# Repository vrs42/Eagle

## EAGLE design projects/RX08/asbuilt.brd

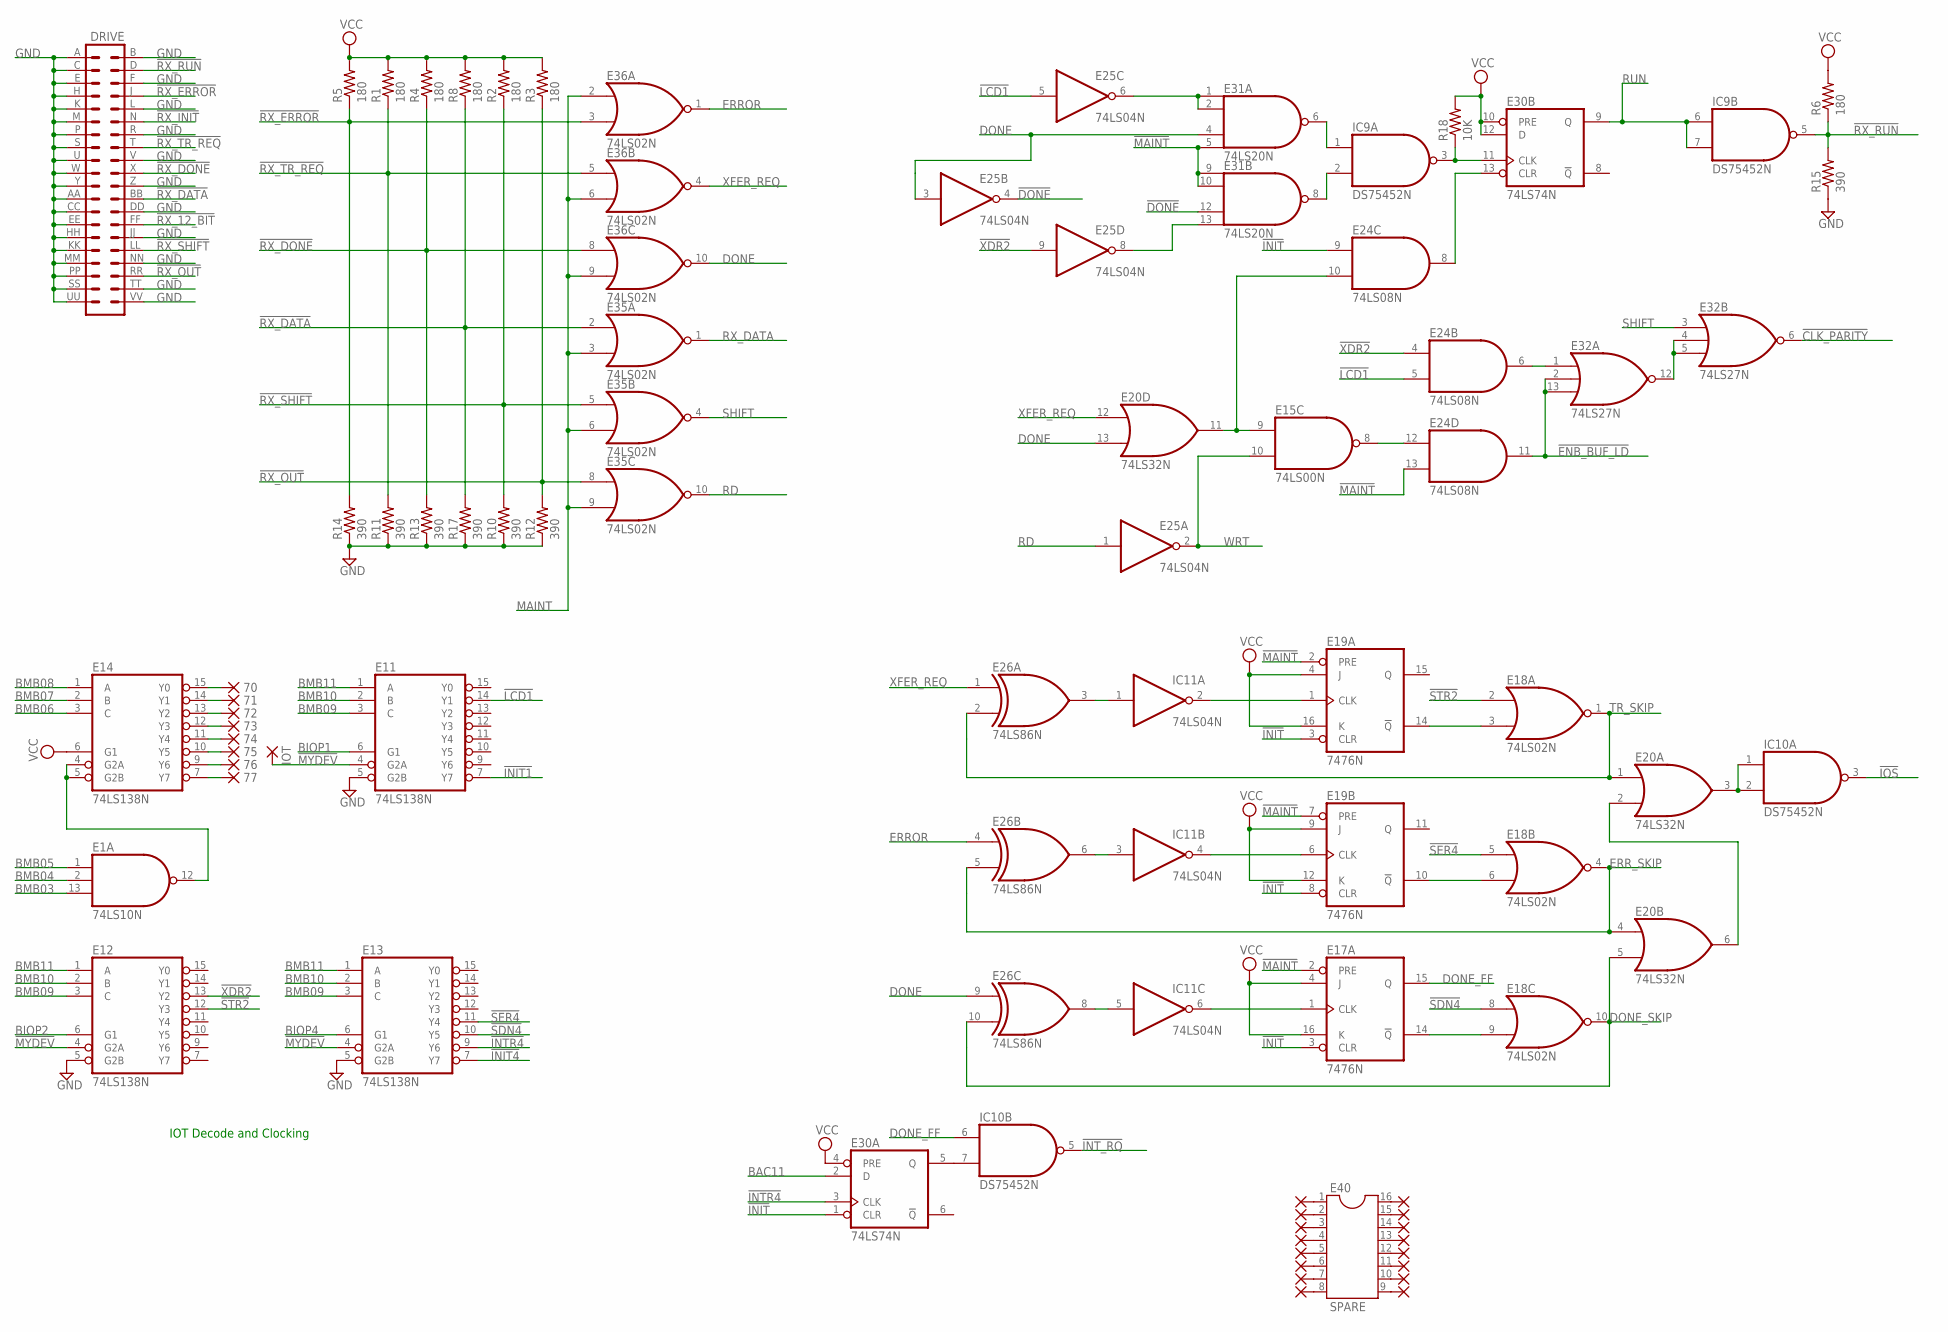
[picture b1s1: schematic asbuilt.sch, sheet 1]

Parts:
70, 71, 72, 73, 74, 75, 76, 77: 1,6/0,8
DRIVE: DEC40PINV
E1: 74LS10N; DIL14
E11, E12, E13, E14: 74LS138N; DIL16
E15: 74LS00N; DIL14
E17, E19: 7476N; DIL16
E18, E35, E36: 74LS02N; DIL14
E20: 74LS32N; DIL14
E24: 74LS08N; DIL14
E25: 74LS04N; DIL14
E26: 74LS86N; DIL14
E30: 74LS74N; DIL14
E31: 74LS20N; DIL14
E32: 74LS27N; DIL14
E40: SPARE; DIL16
IC9, IC10: DS75452N; DIL08
IC11: 74LS04N; DIL14
IOT: 1,6/0,8
PAD18, PAD19, PAD28, PAD29, PAD30, PAD31, PAD32, PAD33, PAD34, PAD35, PAD36, PAD37, PAD38, PAD39, PAD40, PAD41: 1,6/0,8
R1, R2, R3, R4, R5, R6, R8: 180; 0207/10
R10, R11, R12, R13, R14, R15, R17: 390; 0207/10
R18: 10K; 0207/10

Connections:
!CLK_PARITY: E32.6 (O); also elsewhere on the board
!DONE: E25.4 (O), E31.12 (I2); also elsewhere on the board
!ENB_BUF_LD: E24.11 (O), E32.2 (I1), E32.13 (I2); also elsewhere on the board
!INIT: E17.3 (CLR), E19.3 (CLR), E19.8 (CLR), E24.9 (I0), E30.1 (CLR); also elsewhere on the board
!INIT1: E11.7 (Y7); also elsewhere on the board
!INIT4: E13.7 (Y7); also elsewhere on the board
!INTR4: E13.9 (Y6), E30.3 (CLK)
!INT_RQ: IC10.5 (O); also elsewhere on the board
!IOS: IC10.3 (O); also elsewhere on the board
!LCD1: E11.14 (Y1), E24.5 (I1), E25.5 (I); also elsewhere on the board
!MAINT: E17.2 (PRE), E19.2 (PRE), E19.7 (PRE), E24.13 (I1), E31.5 (I3), E31.9 (I0), E31.10 (I1); also elsewhere on the board
!MYDEV: E11.4 (G2A), E12.4 (G2A), E13.4 (G2A), IOT.1
!RX_12_BIT: DRIVE.FF (28); also elsewhere on the board
!RX_DATA: DRIVE.BB (24), E35.2 (I0), R8.1, R17.2; also elsewhere on the board
!RX_DONE: DRIVE.X (20), E36.8 (I0), R4.1, R13.2
!RX_ERROR: DRIVE.J (8), E36.3 (I1), R5.1, R14.2
!RX_INIT: DRIVE.N (12); also elsewhere on the board
!RX_OUT: DRIVE.RR (36), E35.8 (I0), R3.1, R12.2
!RX_RUN: DRIVE.D (4), IC9.5 (O), R6.1, R15.2
!RX_SHIFT: DRIVE.LL (32), E35.5 (I0), R2.1, R10.2
!RX_TR_REQ: DRIVE.T (16), E36.5 (I0), R1.1, R11.2
!SDN4: E13.10 (Y5), E18.8 (I0)
!SER4: E13.11 (Y4), E18.5 (I0)
!STR2: E12.12 (Y3), E18.2 (I0)
!XDR2: E12.13 (Y2), E24.4 (I0), E25.9 (I); also elsewhere on the board
BAC11: E30.2 (D); also elsewhere on the board
BIOP1: E11.6 (G1); also elsewhere on the board
BIOP2: E12.6 (G1); also elsewhere on the board
BIOP4: E13.6 (G1); also elsewhere on the board
BMB03: E1.13 (I2); also elsewhere on the board
BMB04: E1.2 (I1); also elsewhere on the board
BMB05: E1.1 (I0); also elsewhere on the board
BMB06: E14.3 (C); also elsewhere on the board
BMB07: E14.2 (B); also elsewhere on the board
BMB08: E14.1 (A); also elsewhere on the board
BMB09: E11.3 (C), E12.3 (C), E13.3 (C); also elsewhere on the board
BMB10: E11.2 (B), E12.2 (B), E13.2 (B); also elsewhere on the board
BMB11: E11.1 (A), E12.1 (A), E13.1 (A); also elsewhere on the board
DONE: E20.13 (I1), E25.3 (I), E26.9 (I0), E31.4 (I2), E36.10 (O); also elsewhere on the board
DONE_FF: E17.15 (Q), IC10.6 (I0)
DONE_SKIP: E18.10 (O), E20.5 (I1), E26.10 (I1)
ERROR: E26.4 (I0), E36.1 (O)
ERR_SKIP: E18.4 (O), E20.4 (I0), E26.5 (I1)
GND: DRIVE.A (1), DRIVE.AA (23), DRIVE.B (2), DRIVE.C (3), DRIVE.CC (25), DRIVE.DD (26), DRIVE.E (5), DRIVE.EE (27), DRIVE.F (6), DRIVE.H (7), DRIVE.HH (29), DRIVE.JJ (30), DRIVE.K (9), DRIVE.KK (31), DRIVE.L (10), DRIVE.M (11), DRIVE.MM (33), DRIVE.NN (34), DRIVE.P (13), DRIVE.PP (35), DRIVE.R (14), DRIVE.S (15), DRIVE.SS (37), DRIVE.TT (38), DRIVE.U (17), DRIVE.UU (39), DRIVE.V (18), DRIVE.VV (40), DRIVE.W (19), DRIVE.Y (21), DRIVE.Z (22), E1.7 (GND), E11.5 (G2B), E11.8 (GND), E12.5 (G2B), E12.8 (GND), E13.5 (G2B), E13.8 (GND), E14.8 (GND), E15.7 (GND), E17.13 (GND), E18.7 (GND), E19.13 (GND), E20.7 (GND), E24.7 (GND), E25.7 (GND), E26.7 (GND), E30.7 (GND), E31.7 (GND), E32.7 (GND), E35.7 (GND), E36.7 (GND), IC9.4 (GND), IC10.4 (GND), IC11.7 (GND), R10.1, R11.1, R12.1, R13.1, R14.1, R15.1, R17.1; also elsewhere on the board
LCD1: E25.6 (O), E31.1 (I0), E31.2 (I1)
MAINT: E35.3 (I1), E35.6 (I1), E35.9 (I1), E36.2 (I0), E36.6 (I1), E36.9 (I1); also elsewhere on the board
unnamed: 76.1, E14.9 (Y6)
unnamed: 70.1, E14.15 (Y0)
unnamed: 71.1, E14.14 (Y1)
unnamed: 72.1, E14.13 (Y2)
unnamed: 73.1, E14.12 (Y3)
unnamed: 74.1, E14.11 (Y4)
unnamed: 75.1, E14.10 (Y5)
unnamed: 77.1, E14.7 (Y7)
unnamed: E15.9 (I0), E20.11 (O), E24.10 (I1)
unnamed: E15.8 (O), E24.12 (I0)
unnamed: E40.1, PAD18.1
unnamed: E26.8 (O), IC11.5 (I)
unnamed: E40.2, PAD19.1
unnamed: E40.3, PAD28.1
unnamed: E24.6 (O), E32.1 (I0)
unnamed: E1.12 (O), E14.4 (G2A), E14.5 (G2B)
unnamed: E40.4, PAD29.1
unnamed: E40.5, PAD30.1
unnamed: E40.6, PAD31.1
unnamed: E40.7, PAD32.1
unnamed: E40.8, PAD33.1
unnamed: E40.16, PAD34.1
unnamed: E40.15, PAD35.1
unnamed: E40.14, PAD36.1
unnamed: E40.13, PAD37.1
unnamed: E40.12, PAD38.1
unnamed: E40.11, PAD39.1
unnamed: E40.10, PAD40.1
unnamed: E40.9, PAD41.1
unnamed: E30.5 (Q), IC10.7 (I1)
unnamed: E32.4 (I1), E32.5 (I2), E32.12 (O)
unnamed: E20.2 (I1), E20.6 (O)
unnamed: E20.3 (O), IC10.1 (I0), IC10.2 (I1)
unnamed: E19.6 (CLK), IC11.4 (O)
unnamed: E19.1 (CLK), IC11.2 (O)
unnamed: E18.3 (I1), E19.14 (!Q)
unnamed: E18.6 (I1), E19.10 (!Q)
unnamed: E30.11 (CLK), IC9.3 (O), R18.1
unnamed: E31.8 (O), IC9.2 (I1)
unnamed: E17.14 (!Q), E18.9 (I1)
unnamed: E17.1 (CLK), IC11.6 (O)
unnamed: E31.6 (O), IC9.1 (I0)
unnamed: E24.8 (O), E30.13 (CLR)
unnamed: E25.8 (O), E31.13 (I3)
unnamed: E26.6 (O), IC11.3 (I)
unnamed: E26.3 (O), IC11.1 (I)
RD: E25.1 (I), E35.10 (O); also elsewhere on the board
RUN: E30.9 (Q), IC9.6 (I0), IC9.7 (I1); also elsewhere on the board
RX_DATA: E35.1 (O); also elsewhere on the board
SHIFT: E32.3 (I0), E35.4 (O)
TR_SKIP: E18.1 (O), E20.1 (I0), E26.2 (I1)
VCC: E1.14 (VCC), E11.16 (VCC), E12.16 (VCC), E13.16 (VCC), E14.6 (G1), E14.16 (VCC), E15.14 (VCC), E17.4 (J), E17.5 (VCC), E17.16 (K), E18.14 (VCC), E19.4 (J), E19.5 (VCC), E19.9 (J), E19.12 (K), E19.16 (K), E20.14 (VCC), E24.14 (VCC), E25.14 (VCC), E26.14 (VCC), E30.4 (PRE), E30.10 (PRE), E30.12 (D), E30.14 (VCC), E31.14 (VCC), E32.14 (VCC), E35.14 (VCC), E36.14 (VCC), IC9.8 (VCC), IC10.8 (VCC), IC11.14 (VCC), R1.2, R2.2, R3.2, R4.2, R5.2, R6.2, R8.2, R18.2; also elsewhere on the board
WRT: E15.10 (I1), E25.2 (O); also elsewhere on the board
XFER_REQ: E20.12 (I0), E26.1 (I0), E36.4 (O)

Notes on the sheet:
IOT Decode and Clocking

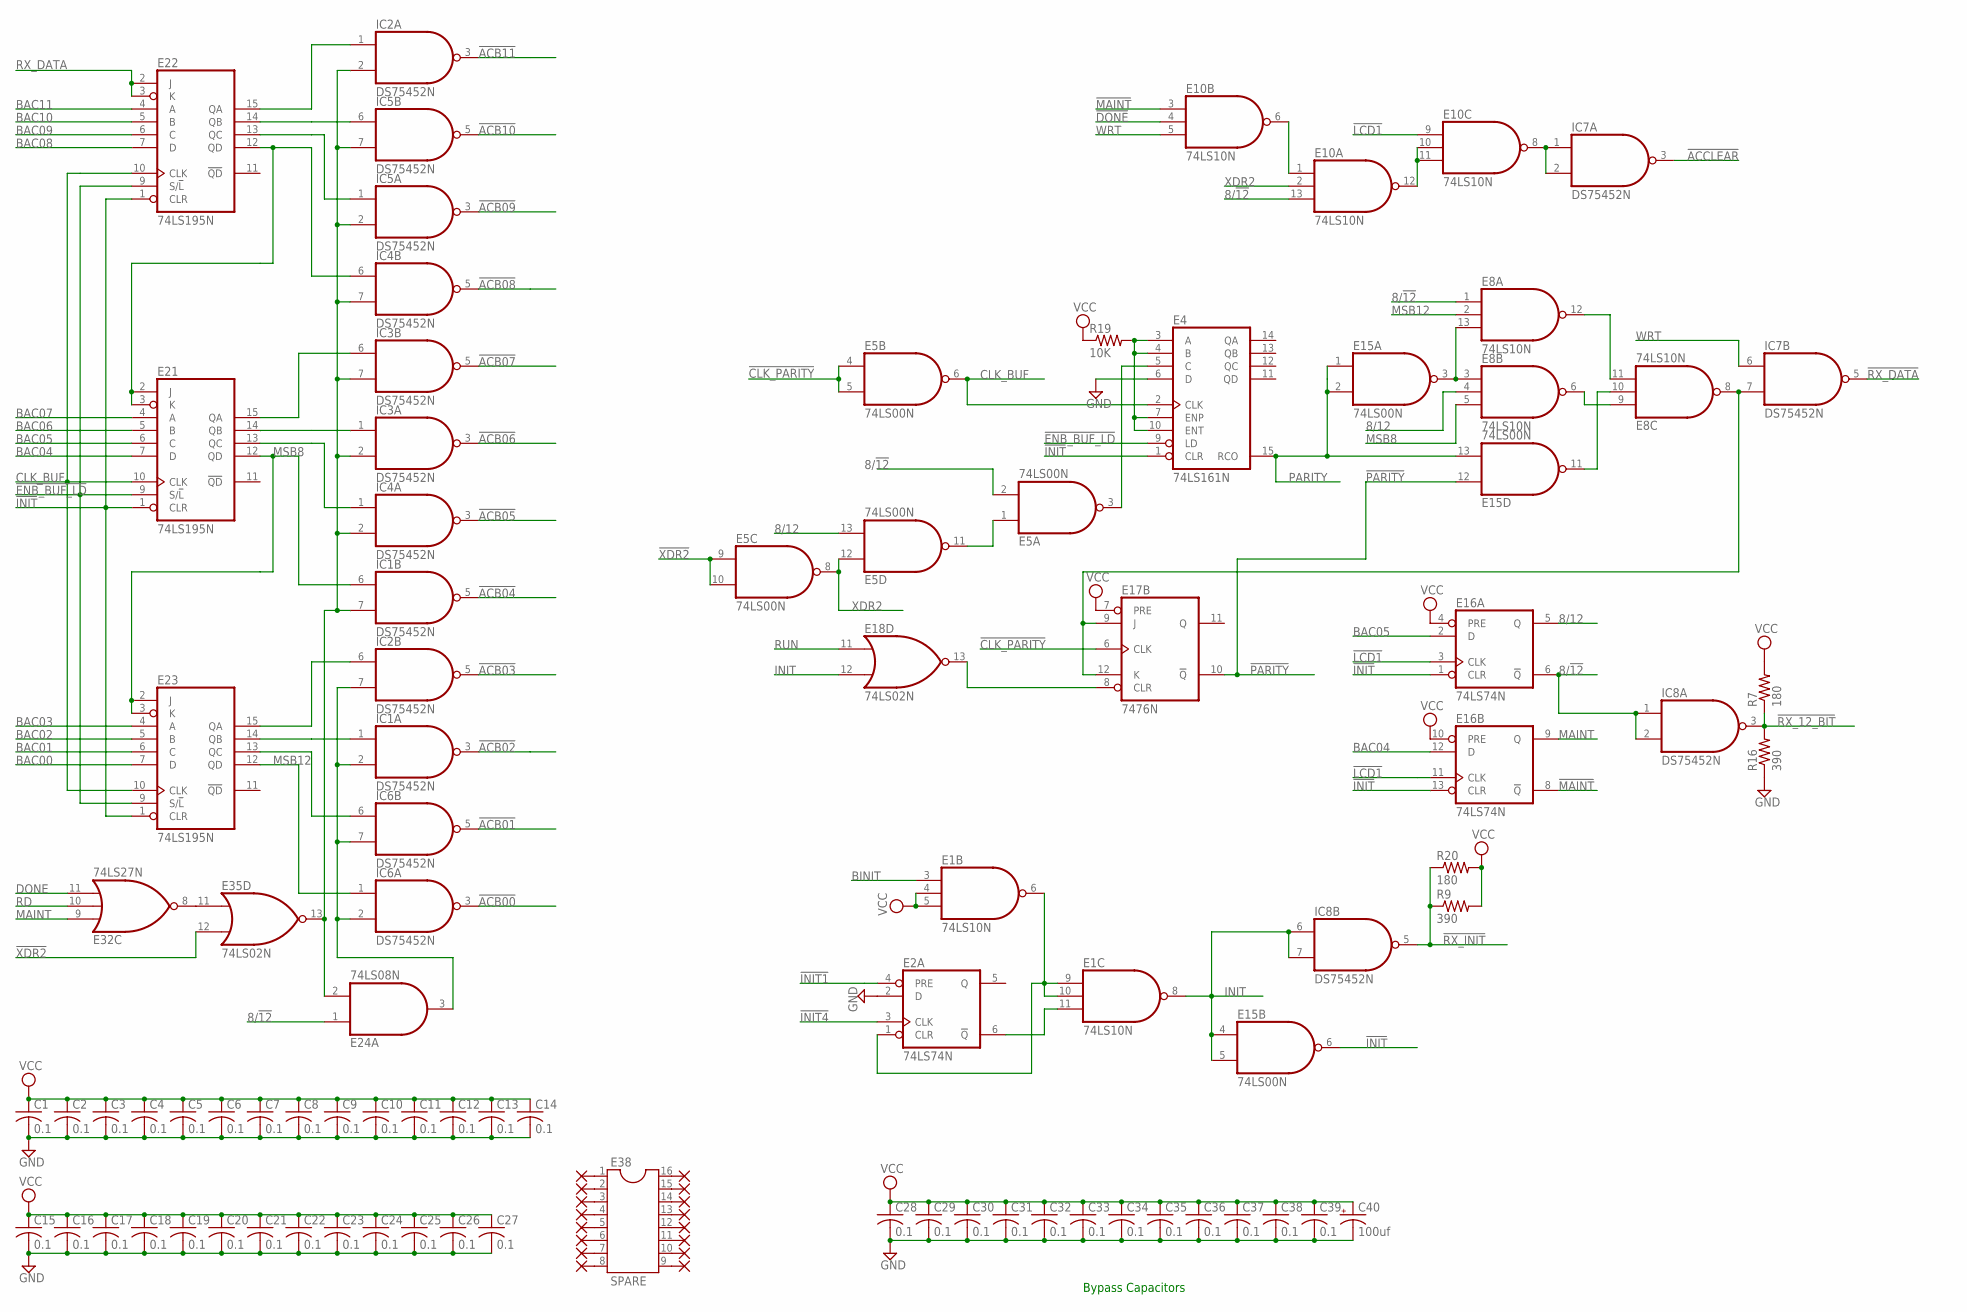
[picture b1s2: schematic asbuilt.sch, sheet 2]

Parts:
C1, C2, C3, C4, C5, C6, C7, C8, C9, C10, C11, C12, C13, C14, C15, C16, C17, C18, C19, C20, C21, C22, C23, C24, C25, C26, C27, C28, C29, C30, C31, C32, C33, C34, C35, C36, C37, C38, C39: 0.1; C050-025X075
C40: 100uf; E22-9
E1, E8, E10: 74LS10N; DIL14
E2, E16: 74LS74N; DIL14
E4: 74LS161N; DIL16
E5, E15: 74LS00N; DIL14
E17: 7476N; DIL16
E18, E35: 74LS02N; DIL14
E21, E22, E23: 74LS195N; DIL16
E24: 74LS08N; DIL14
E32: 74LS27N; DIL14
E38: SPARE; DIL16
IC1, IC2, IC3, IC4, IC5, IC6, IC7, IC8: DS75452N; DIL08
PAD10, PAD11, PAD12, PAD13, PAD14, PAD15, PAD16, PAD17, PAD20, PAD21, PAD22, PAD23, PAD24, PAD25, PAD26, PAD27: 1,6/0,8
R7, R20: 180; 0207/10
R9, R16: 390; 0207/10
R19: 10K; 0207/10

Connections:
8/12: E5.13 (I1), E8.4 (I1), E16.5 (Q)
8/!12: E5.2 (I1), E8.1 (I0), E10.13 (I2), E16.6 (!Q), E24.1 (I0), IC8.1 (I0), IC8.2 (I1)
!ACB00: IC6.3 (O); also elsewhere on the board
!ACB01: IC6.5 (O); also elsewhere on the board
!ACB02: IC1.3 (O); also elsewhere on the board
!ACB03: IC2.5 (O); also elsewhere on the board
!ACB04: IC1.5 (O); also elsewhere on the board
!ACB05: IC4.3 (O); also elsewhere on the board
!ACB06: IC3.3 (O); also elsewhere on the board
!ACB07: IC3.5 (O); also elsewhere on the board
!ACB08: IC4.5 (O); also elsewhere on the board
!ACB09: IC5.3 (O); also elsewhere on the board
!ACB10: IC5.5 (O); also elsewhere on the board
!ACB11: IC2.3 (O); also elsewhere on the board
!ACCLEAR: IC7.3 (O); also elsewhere on the board
!CLK_PARITY: E5.4 (I0), E5.5 (I1), E17.6 (CLK); also elsewhere on the board
!DONE: E10.4 (I1); also elsewhere on the board
!ENB_BUF_LD: E4.9 (LD), E21.9 (S/!L), E22.9 (S/!L), E23.9 (S/!L); also elsewhere on the board
!INIT: E4.1 (CLR), E15.6 (O), E16.1 (CLR), E16.13 (CLR), E21.1 (CLR), E22.1 (CLR), E23.1 (CLR); also elsewhere on the board
!INIT1: E2.4 (PRE); also elsewhere on the board
!INIT4: E2.3 (CLK); also elsewhere on the board
!LCD1: E10.9 (I0), E16.3 (CLK), E16.11 (CLK); also elsewhere on the board
!MAINT: E10.3 (I0), E16.8 (!Q); also elsewhere on the board
!PARITY: E15.12 (I0), E17.10 (!Q)
!RX_12_BIT: IC8.3 (O), R7.1, R16.2; also elsewhere on the board
!RX_DATA: IC7.5 (O); also elsewhere on the board
!RX_INIT: IC8.5 (O), R9.1, R20.1; also elsewhere on the board
!XDR2: E5.9 (I0), E5.10 (I1), E35.12 (I1); also elsewhere on the board
BAC00: E23.7 (D); also elsewhere on the board
BAC01: E23.6 (C); also elsewhere on the board
BAC02: E23.5 (B); also elsewhere on the board
BAC03: E23.4 (A); also elsewhere on the board
BAC04: E16.12 (D), E21.7 (D); also elsewhere on the board
BAC05: E16.2 (D), E21.6 (C); also elsewhere on the board
BAC06: E21.5 (B); also elsewhere on the board
BAC07: E21.4 (A); also elsewhere on the board
BAC08: E22.7 (D); also elsewhere on the board
BAC09: E22.6 (C); also elsewhere on the board
BAC10: E22.5 (B); also elsewhere on the board
BAC11: E22.4 (A); also elsewhere on the board
BINIT: E1.3 (I0); also elsewhere on the board
CLK_BUF: E4.2 (CLK), E5.6 (O), E21.10 (CLK), E22.10 (CLK), E23.10 (CLK)
DONE: E32.11 (I2); also elsewhere on the board
GND: C1.2, C2.2, C3.2, C4.2, C5.2, C6.2, C7.2, C8.2, C9.2, C10.2, C11.2, C12.2, C13.2, C14.2, C15.2, C16.2, C17.2, C18.2, C19.2, C20.2, C21.2, C22.2, C23.2, C24.2, C25.2, C26.2, C27.2, C28.2, C29.2, C30.2, C31.2, C32.2, C33.2, C34.2, C35.2, C36.2, C37.2, C38.2, C39.2, C40.-, E1.7 (GND), E2.2 (D), E2.7 (GND), E4.6 (D), E4.8 (GND), E5.7 (GND), E8.7 (GND), E10.7 (GND), E15.7 (GND), E16.7 (GND), E17.13 (GND), E18.7 (GND), E21.8 (GND), E22.8 (GND), E23.8 (GND), E24.7 (GND), E32.7 (GND), E35.7 (GND), IC1.4 (GND), IC2.4 (GND), IC3.4 (GND), IC4.4 (GND), IC5.4 (GND), IC6.4 (GND), IC7.4 (GND), IC8.4 (GND), R16.1; also elsewhere on the board
INIT: E1.8 (O), E15.4 (I0), E15.5 (I1), E18.12 (I1), IC8.6 (I0), IC8.7 (I1)
MAINT: E16.9 (Q), E32.9 (I0); also elsewhere on the board
MSB8: E8.5 (I2), E21.12 (QD), E23.2 (J), E23.3 (K), IC1.6 (I0)
MSB12: E8.2 (I1), E23.12 (QD), IC6.1 (I0)
unnamed: E23.14 (QB), IC1.1 (I0)
unnamed: E24.2 (I1), E35.13 (O), IC1.7 (I1), IC2.2 (I1), IC3.2 (I1), IC3.7 (I1), IC4.2 (I1), IC4.7 (I1), IC5.2 (I1), IC5.7 (I1)
unnamed: E32.8 (O), E35.11 (I0)
unnamed: E24.3 (O), IC1.2 (I1), IC2.7 (I1), IC6.2 (I1), IC6.7 (I1)
unnamed: E38.1, PAD10.1
unnamed: E38.2, PAD11.1
unnamed: E38.3, PAD12.1
unnamed: E38.4, PAD13.1
unnamed: E38.5, PAD14.1
unnamed: E38.6, PAD15.1
unnamed: E38.7, PAD16.1
unnamed: E38.8, PAD17.1
unnamed: E4.5 (C), E5.3 (O)
unnamed: E38.16, PAD20.1
unnamed: E38.15, PAD21.1
unnamed: E38.14, PAD22.1
unnamed: E38.13, PAD23.1
unnamed: E38.12, PAD24.1
unnamed: E38.11, PAD25.1
unnamed: E38.10, PAD26.1
unnamed: E38.9, PAD27.1
unnamed: E21.2 (J), E21.3 (K), E22.12 (QD), IC4.6 (I0)
unnamed: E23.13 (QC), IC6.6 (I0)
unnamed: E5.1 (I0), E5.11 (O)
unnamed: E8.3 (I0), E8.13 (I2), E15.3 (O)
unnamed: E8.11 (I2), E8.12 (O)
unnamed: E8.6 (O), E8.9 (I0)
unnamed: E8.10 (I1), E15.11 (O)
unnamed: E8.8 (O), E17.9 (J), E17.12 (K), IC7.7 (I1)
unnamed: E1.11 (I2), E2.6 (!Q)
unnamed: E17.8 (CLR), E18.13 (O)
unnamed: E1.6 (O), E1.9 (I0), E1.10 (I1), E2.1 (CLR)
unnamed: E4.3 (A), E4.4 (B), E4.7 (ENP), E4.10 (ENT), R19.2
unnamed: E23.15 (QA), IC2.6 (I0)
unnamed: E21.13 (QC), IC4.1 (I0)
unnamed: E21.14 (QB), IC3.1 (I0)
unnamed: E21.15 (QA), IC3.6 (I0)
unnamed: E22.15 (QA), IC2.1 (I0)
unnamed: E22.13 (QC), IC5.1 (I0)
unnamed: E22.14 (QB), IC5.6 (I0)
unnamed: E10.1 (I0), E10.6 (O)
unnamed: E10.10 (I1), E10.11 (I2), E10.12 (O)
unnamed: E10.8 (O), IC7.1 (I0), IC7.2 (I1)
PARITY: E4.15 (RCO), E15.1 (I0), E15.2 (I1), E15.13 (I1)
RD: E32.10 (I1); also elsewhere on the board
RUN: E18.11 (I0); also elsewhere on the board
RX_DATA: E22.2 (J), E22.3 (K); also elsewhere on the board
VCC: C1.1, C2.1, C3.1, C4.1, C5.1, C6.1, C7.1, C8.1, C9.1, C10.1, C11.1, C12.1, C13.1, C14.1, C15.1, C16.1, C17.1, C18.1, C19.1, C20.1, C21.1, C22.1, C23.1, C24.1, C25.1, C26.1, C27.1, C28.1, C29.1, C30.1, C31.1, C32.1, C33.1, C34.1, C35.1, C36.1, C37.1, C38.1, C39.1, C40.+, E1.4 (I1), E1.5 (I2), E1.14 (VCC), E2.14 (VCC), E4.16 (VCC), E5.14 (VCC), E8.14 (VCC), E10.14 (VCC), E15.14 (VCC), E16.4 (PRE), E16.10 (PRE), E16.14 (VCC), E17.5 (VCC), E17.7 (PRE), E18.14 (VCC), E21.16 (VCC), E22.16 (VCC), E23.16 (VCC), E24.14 (VCC), E32.14 (VCC), E35.14 (VCC), IC1.8 (VCC), IC2.8 (VCC), IC3.8 (VCC), IC4.8 (VCC), IC5.8 (VCC), IC6.8 (VCC), IC7.8 (VCC), IC8.8 (VCC), R7.2, R9.2, R19.1, R20.2; also elsewhere on the board
WRT: E10.5 (I2), IC7.6 (I0); also elsewhere on the board
XDR2: E5.8 (O), E5.12 (I0), E10.2 (I1)

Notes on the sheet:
Bypass Capacitors

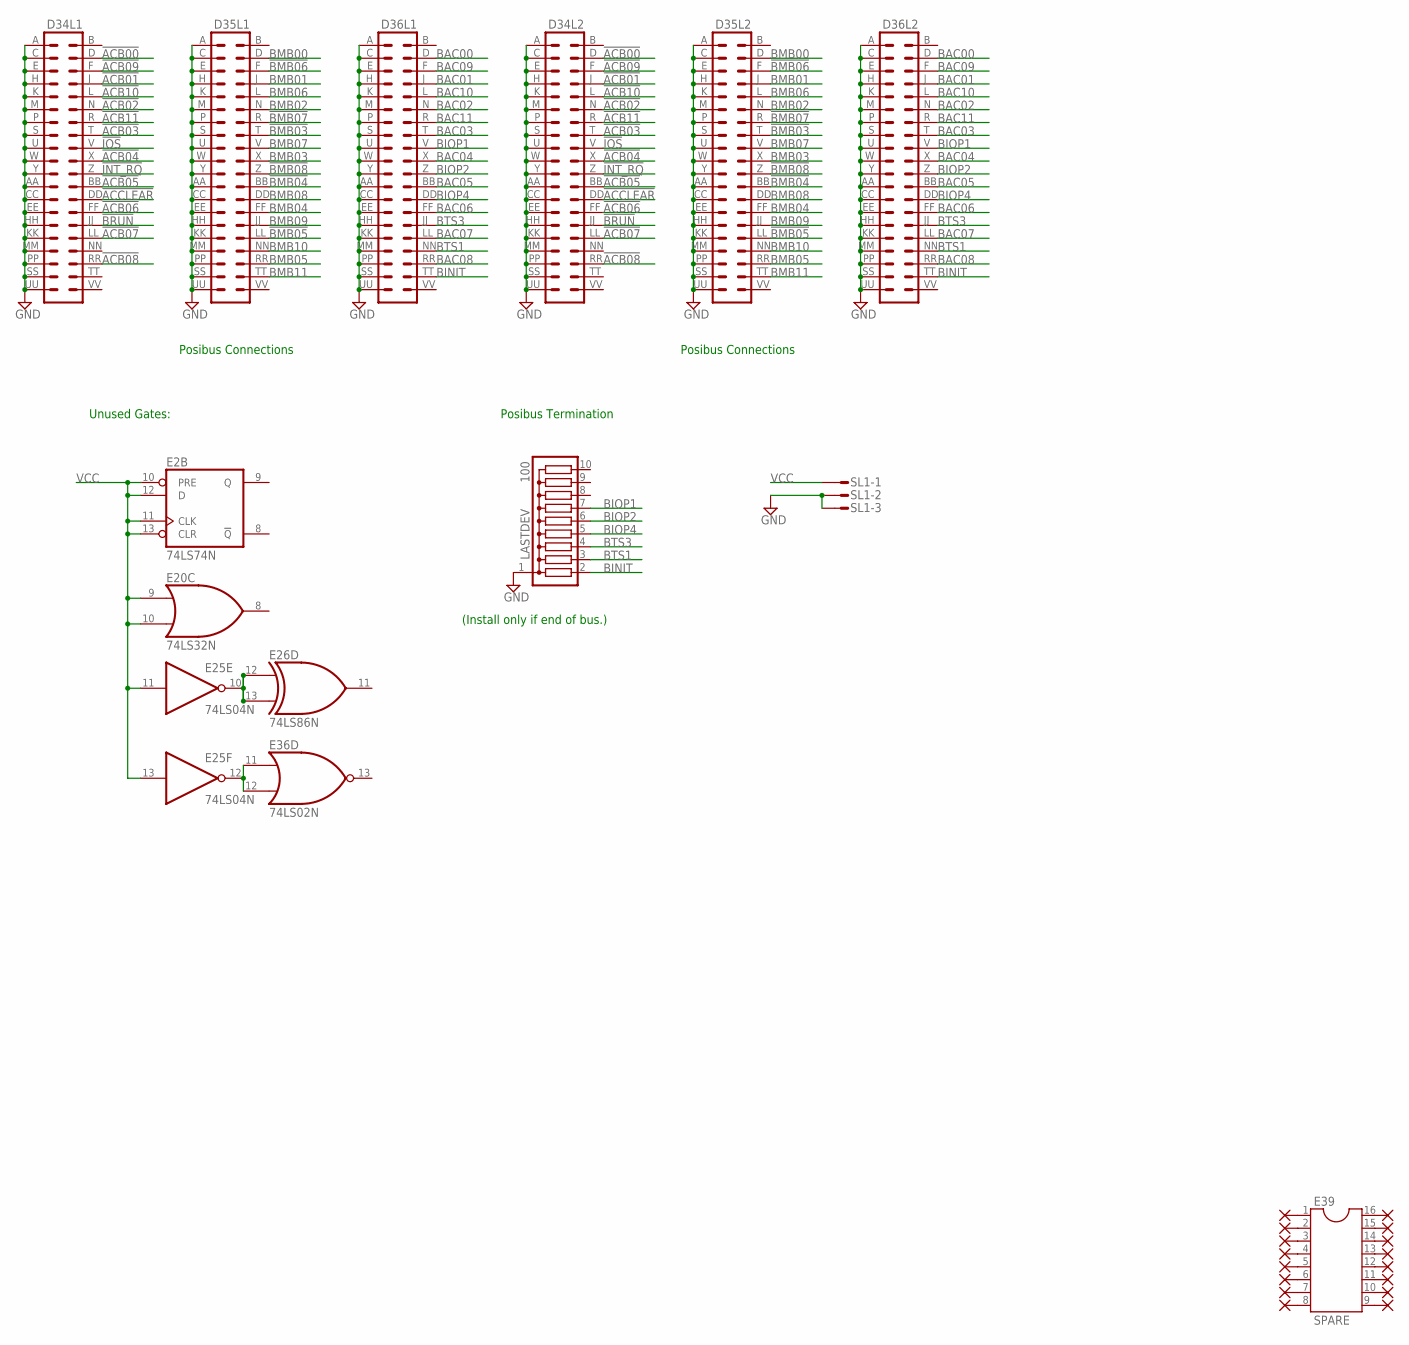
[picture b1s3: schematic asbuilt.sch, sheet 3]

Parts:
D34L1, D34L2, D35L1, D35L2, D36L1, D36L2: DEC40PINV
E2: 74LS74N; DIL14
E20: 74LS32N; DIL14
E25: 74LS04N; DIL14
E26: 74LS86N; DIL14
E36: 74LS02N; DIL14
E39: SPARE; DIL16
LASTDEV: 100; SIL10
PAD42, PAD43, PAD44, PAD45, PAD46, PAD47, PAD48, PAD49, PAD50, PAD51, PAD52, PAD53, PAD54, PAD55, PAD56, PAD57: 1,6/0,8
SL1: MA04S; 04PA

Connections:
!ACB00: D34L1.D (4), D34L2.D (4); also elsewhere on the board
!ACB01: D34L1.J (8), D34L2.J (8); also elsewhere on the board
!ACB02: D34L1.N (12), D34L2.N (12); also elsewhere on the board
!ACB03: D34L1.T (16), D34L2.T (16); also elsewhere on the board
!ACB04: D34L1.X (20), D34L2.X (20); also elsewhere on the board
!ACB05: D34L1.BB (24), D34L2.BB (24); also elsewhere on the board
!ACB06: D34L1.FF (28), D34L2.FF (28); also elsewhere on the board
!ACB07: D34L1.LL (32), D34L2.LL (32); also elsewhere on the board
!ACB08: D34L1.RR (36), D34L2.RR (36); also elsewhere on the board
!ACB09: D34L1.F (6), D34L2.F (6); also elsewhere on the board
!ACB10: D34L1.L (10), D34L2.L (10); also elsewhere on the board
!ACB11: D34L1.R (14), D34L2.R (14); also elsewhere on the board
!ACCLEAR: D34L1.DD (26), D34L2.DD (26); also elsewhere on the board
!BMB03: D35L1.T (16), D35L2.T (16)
!BMB04: D35L1.BB (24), D35L2.BB (24)
!BMB05: D35L1.LL (32), D35L2.LL (32)
!BMB06: D35L1.F (6), D35L2.F (6)
!BMB07: D35L1.R (14), D35L2.R (14)
!BMB08: D35L1.Z (22), D35L2.Z (22)
!BRUN: D34L1.JJ (30), D34L2.JJ (30)
!INT_RQ: D34L1.Z (22), D34L2.Z (22); also elsewhere on the board
!IOS: D34L1.V (18), D34L2.V (18); also elsewhere on the board
BAC00: D36L1.D (4), D36L2.D (4); also elsewhere on the board
BAC01: D36L1.J (8), D36L2.J (8); also elsewhere on the board
BAC02: D36L1.N (12), D36L2.N (12); also elsewhere on the board
BAC03: D36L1.T (16), D36L2.T (16); also elsewhere on the board
BAC04: D36L1.X (20), D36L2.X (20); also elsewhere on the board
BAC05: D36L1.BB (24), D36L2.BB (24); also elsewhere on the board
BAC06: D36L1.FF (28), D36L2.FF (28); also elsewhere on the board
BAC07: D36L1.LL (32), D36L2.LL (32); also elsewhere on the board
BAC08: D36L1.RR (36), D36L2.RR (36); also elsewhere on the board
BAC09: D36L1.F (6), D36L2.F (6); also elsewhere on the board
BAC10: D36L1.L (10), D36L2.L (10); also elsewhere on the board
BAC11: D36L1.R (14), D36L2.R (14); also elsewhere on the board
BINIT: D36L1.TT (38), D36L2.TT (38), LASTDEV.2; also elsewhere on the board
BIOP1: D36L1.V (18), D36L2.V (18), LASTDEV.7; also elsewhere on the board
BIOP2: D36L1.Z (22), D36L2.Z (22), LASTDEV.6; also elsewhere on the board
BIOP4: D36L1.DD (26), D36L2.DD (26), LASTDEV.5; also elsewhere on the board
BMB00: D35L1.D (4), D35L2.D (4)
BMB01: D35L1.J (8), D35L2.J (8)
BMB02: D35L1.N (12), D35L2.N (12)
BMB03: D35L1.X (20), D35L2.X (20); also elsewhere on the board
BMB04: D35L1.FF (28), D35L2.FF (28); also elsewhere on the board
BMB05: D35L1.RR (36), D35L2.RR (36); also elsewhere on the board
BMB06: D35L1.L (10), D35L2.L (10); also elsewhere on the board
BMB07: D35L1.V (18), D35L2.V (18); also elsewhere on the board
BMB08: D35L1.DD (26), D35L2.DD (26); also elsewhere on the board
BMB09: D35L1.JJ (30), D35L2.JJ (30); also elsewhere on the board
BMB10: D35L1.NN (34), D35L2.NN (34); also elsewhere on the board
BMB11: D35L1.TT (38), D35L2.TT (38); also elsewhere on the board
BTS1: D36L1.NN (34), D36L2.NN (34), LASTDEV.3
BTS3: D36L1.JJ (30), D36L2.JJ (30), LASTDEV.4
GND: D34L1.A (1), D34L1.AA (23), D34L1.C (3), D34L1.CC (25), D34L1.E (5), D34L1.EE (27), D34L1.H (7), D34L1.HH (29), D34L1.K (9), D34L1.KK (31), D34L1.M (11), D34L1.MM (33), D34L1.P (13), D34L1.PP (35), D34L1.S (15), D34L1.SS (37), D34L1.U (17), D34L1.UU (39), D34L1.W (19), D34L1.Y (21), D34L2.A (1), D34L2.AA (23), D34L2.C (3), D34L2.CC (25), D34L2.E (5), D34L2.EE (27), D34L2.H (7), D34L2.HH (29), D34L2.K (9), D34L2.KK (31), D34L2.M (11), D34L2.MM (33), D34L2.P (13), D34L2.PP (35), D34L2.S (15), D34L2.SS (37), D34L2.U (17), D34L2.UU (39), D34L2.W (19), D34L2.Y (21), D35L1.A (1), D35L1.AA (23), D35L1.C (3), D35L1.CC (25), D35L1.E (5), D35L1.EE (27), D35L1.H (7), D35L1.HH (29), D35L1.K (9), D35L1.KK (31), D35L1.M (11), D35L1.MM (33), D35L1.P (13), D35L1.PP (35), D35L1.S (15), D35L1.SS (37), D35L1.U (17), D35L1.UU (39), D35L1.W (19), D35L1.Y (21), D35L2.A (1), D35L2.AA (23), D35L2.C (3), D35L2.CC (25), D35L2.E (5), D35L2.EE (27), D35L2.H (7), D35L2.HH (29), D35L2.K (9), D35L2.KK (31), D35L2.M (11), D35L2.MM (33), D35L2.P (13), D35L2.PP (35), D35L2.S (15), D35L2.SS (37), D35L2.U (17), D35L2.UU (39), D35L2.W (19), D35L2.Y (21), D36L1.A (1), D36L1.AA (23), D36L1.C (3), D36L1.CC (25), D36L1.E (5), D36L1.EE (27), D36L1.H (7), D36L1.HH (29), D36L1.K (9), D36L1.KK (31), D36L1.M (11), D36L1.MM (33), D36L1.P (13), D36L1.PP (35), D36L1.S (15), D36L1.SS (37), D36L1.U (17), D36L1.UU (39), D36L1.W (19), D36L1.Y (21), D36L2.A (1), D36L2.AA (23), D36L2.C (3), D36L2.CC (25), D36L2.E (5), D36L2.EE (27), D36L2.H (7), D36L2.HH (29), D36L2.K (9), D36L2.KK (31), D36L2.M (11), D36L2.MM (33), D36L2.P (13), D36L2.PP (35), D36L2.S (15), D36L2.SS (37), D36L2.U (17), D36L2.UU (39), D36L2.W (19), D36L2.Y (21), E2.7 (GND), E20.7 (GND), E25.7 (GND), E26.7 (GND), E36.7 (GND), LASTDEV.1, SL1.2, SL1.3; also elsewhere on the board
unnamed: E39.1, PAD42.1
unnamed: E39.2, PAD43.1
unnamed: E39.3, PAD44.1
unnamed: E39.4, PAD45.1
unnamed: E39.5, PAD46.1
unnamed: E39.6, PAD47.1
unnamed: E39.7, PAD48.1
unnamed: E39.8, PAD49.1
unnamed: E39.16, PAD50.1
unnamed: E39.15, PAD51.1
unnamed: E39.14, PAD52.1
unnamed: E39.13, PAD53.1
unnamed: E39.12, PAD54.1
unnamed: E39.11, PAD55.1
unnamed: E39.10, PAD56.1
unnamed: E39.9, PAD57.1
unnamed: E25.10 (O), E26.12 (I0), E26.13 (I1)
unnamed: E25.12 (O), E36.11 (I0), E36.12 (I1)
VCC: E2.10 (PRE), E2.11 (CLK), E2.12 (D), E2.13 (CLR), E2.14 (VCC), E20.9 (I0), E20.10 (I1), E20.14 (VCC), E25.11 (I), E25.13 (I), E25.14 (VCC), E26.14 (VCC), E36.14 (VCC), SL1.1; also elsewhere on the board

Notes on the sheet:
Posibus Connections
Unused Gates:
Posibus Termination
(Install only if end of bus.)

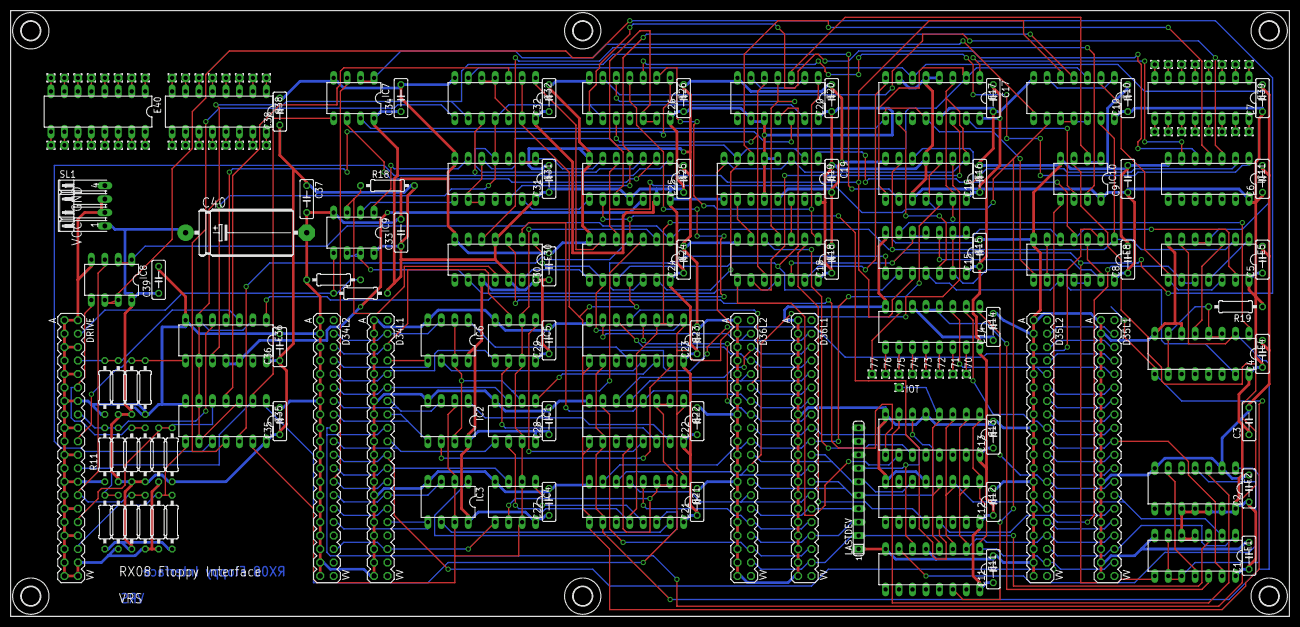
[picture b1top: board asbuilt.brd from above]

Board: 2 copper layers, 241.3 x 114.3 mm, 173 parts (0 on the bottom side), 207 nets.

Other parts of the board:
U$1, U$2, U$3, U$4, U$5, U$6: 3,6

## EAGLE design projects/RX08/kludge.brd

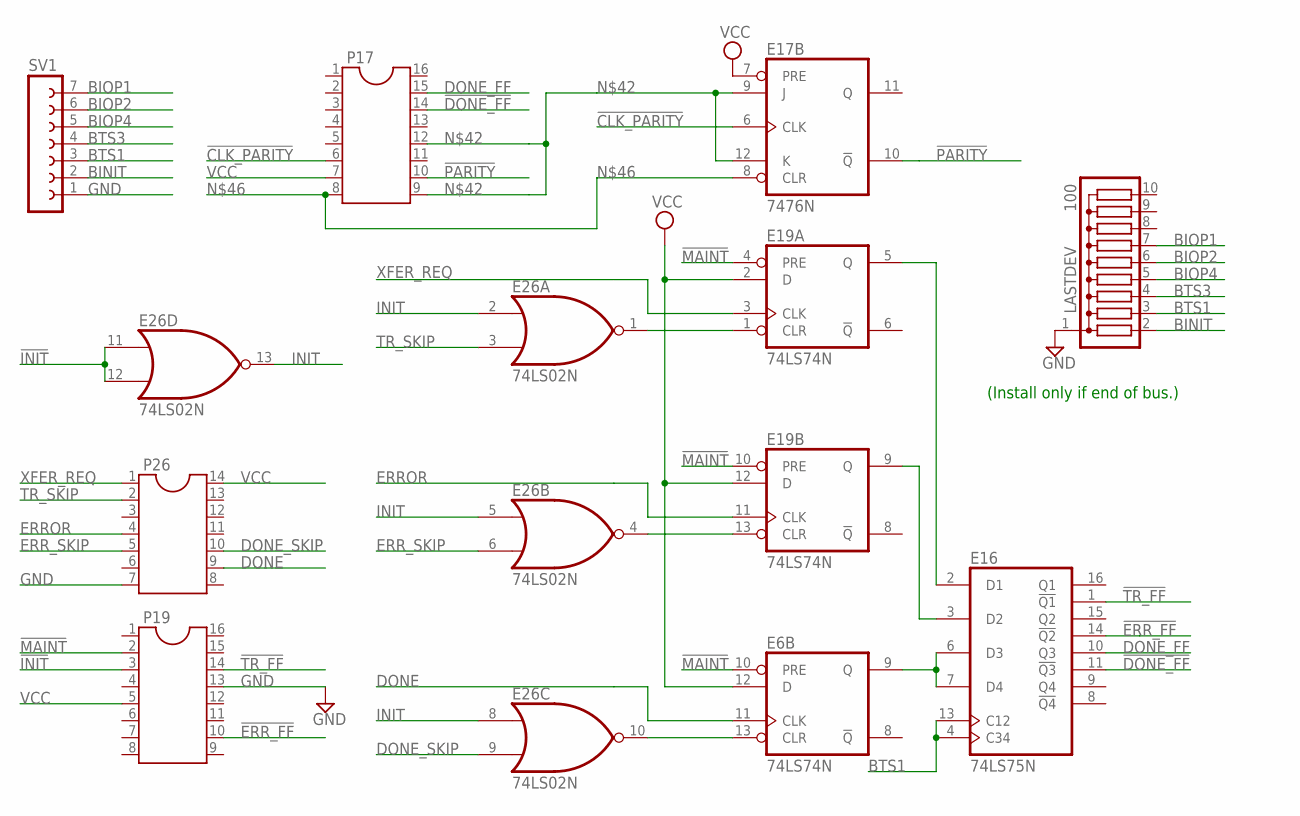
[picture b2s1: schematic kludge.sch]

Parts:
E6, E19: 74LS74N; DIL14
E16: 74LS75N; DIL16
E17: 7476N; DIL16
E26: 74LS02N; DIL14
LASTDEV: 100; SIL10
P17, P19: DIL16
P26: DIL14
SV1: FE07-1; FE07

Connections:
!CLK_PARITY: E17.6 (CLK), P17.6
!DONE_FF: E16.11 (!Q3), P17.14
!ERR_FF: E16.14 (!Q2), P19.10
!INIT: E26.11 (I0), E26.12 (I1), P19.3
!MAINT: E6.10 (PRE), E19.4 (PRE), E19.10 (PRE), P19.2
!PARITY: E17.10 (!Q), P17.10
!TR_FF: E16.1 (!Q1), P19.14
BINIT: LASTDEV.2, SV1.2
BIOP1: LASTDEV.7, SV1.7
BIOP2: LASTDEV.6, SV1.6
BIOP4: LASTDEV.5, SV1.5
BTS1: E16.4 (C34), E16.13 (C12), LASTDEV.3, SV1.3
BTS3: LASTDEV.4, SV1.4
DONE: E6.11 (CLK), P26.9
DONE_FF: E16.10 (Q3), P17.15
DONE_SKIP: E26.9 (I1), P26.10
ERROR: E19.11 (CLK), P26.4
ERR_SKIP: E26.6 (I1), P26.5
GND: E6.7 (GND), E16.12 (GND), E17.13 (GND), E19.7 (GND), E26.7 (GND), LASTDEV.1, P19.13, P26.7, SV1.1
INIT: E26.2 (I0), E26.5 (I0), E26.8 (I0), E26.13 (O)
unnamed: E17.9 (J), E17.12 (K), P17.9, P17.12
unnamed: E17.8 (CLR), P17.8
unnamed: E16.2 (D1), E19.5 (Q)
unnamed: E16.3 (D2), E19.9 (Q)
unnamed: E6.9 (Q), E16.6 (D3), E16.7 (D4)
unnamed: E19.1 (CLR), E26.1 (O)
unnamed: E19.13 (CLR), E26.4 (O)
unnamed: E6.13 (CLR), E26.10 (O)
TR_SKIP: E26.3 (I1), P26.2
VCC: E6.12 (D), E6.14 (VCC), E16.5 (VCC), E17.5 (VCC), E17.7 (PRE), E19.2 (D), E19.12 (D), E19.14 (VCC), E26.14 (VCC), P17.7, P19.5, P26.14
XFER_REQ: E19.3 (CLK), P26.1

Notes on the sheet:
(Install only if end of bus.)

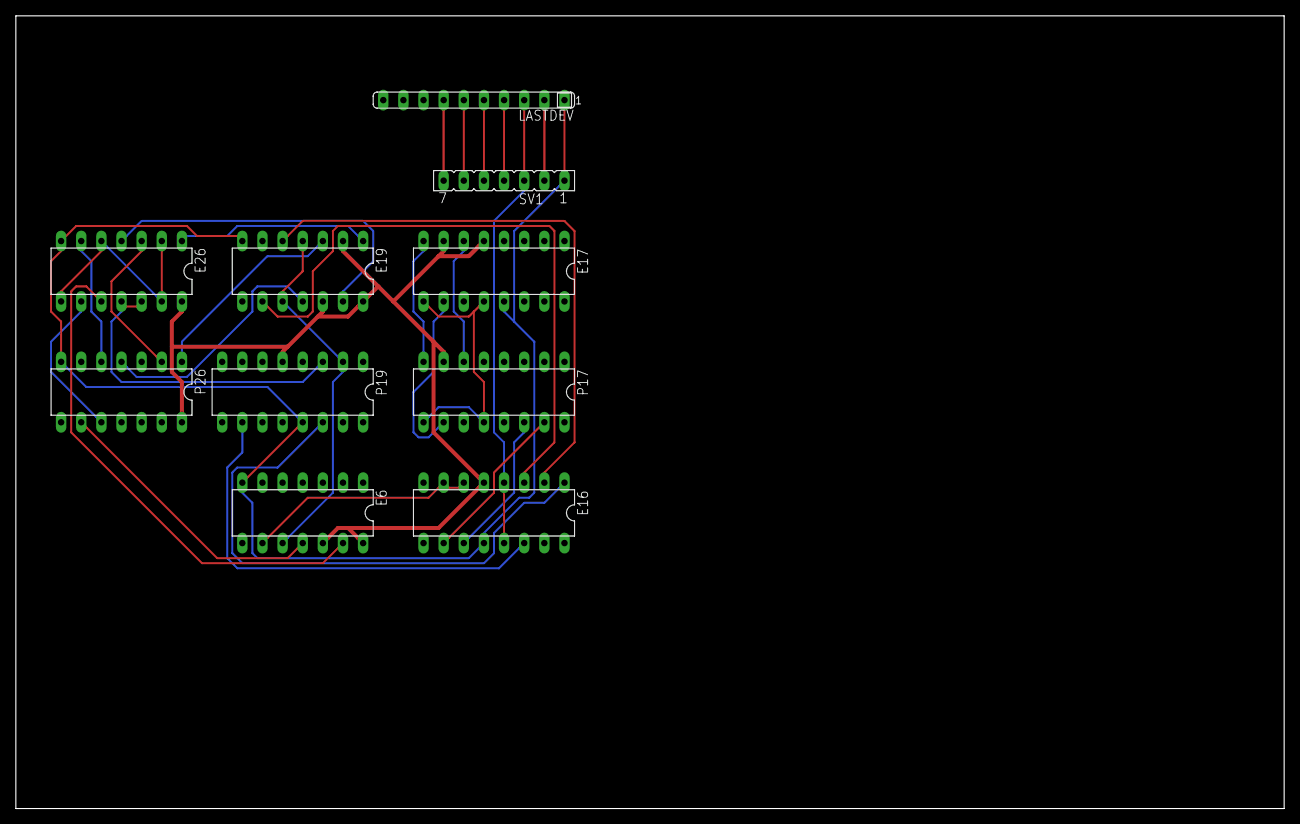
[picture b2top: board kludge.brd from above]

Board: 2 copper layers, 160.0 x 100.0 mm, 10 parts (0 on the bottom side), 31 nets.

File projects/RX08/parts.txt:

Partlist

Exported from kludge.brd at  8/14/2005 10:45:08a

EAGLE Version 4.11 Copyright (c) 1988-2003 CadSoft

Part     Value          Package  Library      Position (inch)       Orientation

E6       74LS74N        DIL14    74xx-us      (1.4 1.45)            R180
E16      74LS75N        DIL16    74xx-us      (2.35 1.45)           R180
E17      74LS76N        DIL16    74xx-jameco  (2.35 2.65)           R180
E19      74LS74N        DIL14    74xx-us      (1.4 2.65)            R180
E26      74LS02N        DIL14    74xx-us      (0.5 2.65)            R180
LASTDEV  100            SIL10    resistor-sil (2.25 3.5)            R180
P17                     DIL16    ic-package   (2.35 2.05)           R180
P19                     DIL16    ic-package   (1.35 2.05)           R180
P26                     DIL14    ic-package   (0.5 2.05)            R180
SV1                     FE07     con-lsta     (2.4 3.1)             R180
